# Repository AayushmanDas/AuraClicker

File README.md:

# ⚡ AuraClicker

A compact, battery-powered custom macro-pad and wireless input controller powered by the **ESP32-C3** RISC-V microcontroller. 

Designed natively in **KiCad** with end-to-end Design for Manufacturing (DFM) verification, ready for turnkey fabrication and assembly via JLCPCB SMT services.

---

## 📸 Media & Previews

| 3D PCB Preview | JLCPCB DFM Placement |
| :---: | :---: |
|  |  |

---

## ✨ Key Features

* **MCU Core:** ESP32-C3 RISC-V SoC (2.4 GHz Wi-Fi & Bluetooth 5 LE).
* **Power & Battery Management:**
  * Dedicated **TP4056** Li-Po linear charging IC over USB-C.
  * **AMS1117-3.3** high-current LDO for clean 3.3V power distribution.
  * 2-Pin **Molex PicoBlade (1.25mm)** battery connector. Recommended to be used with 3.7-4.2V 500mAh LiPo battery.
  * Hardware SPDT power slide switch (`SW1`).
* **Inputs & Peripherals:**
  * 4x Low-profile tactile click buttons (`SW2` – `SW5`) arranged for ergonomic thumb/finger reach.
  * Status LEDs for battery activity and low-power telemetry.
* **Programming & Debugging:**
  * Standard 1x6 (2.54mm) FTDI / UART header (`BERG1`) for serial programming and debug monitoring.

---

## 🗂️ Repository Structure

```text
AuraClicker/
├── kicad/                        # Raw KiCad project and PCB design files
│   ├── AuraClicker.kicad_pro
│   ├── AuraClicker.kicad_sch
│   ├── AuraClicker.kicad_pcb
│   ├── fp-lib-table
│   └── Team_Antarez_Logo.kicad_mod
│
├── production/                   # Fabrication-ready packages & CAD files
│   ├── AuraClicker_Fabrication.zip   # Gerber package ready for JLCPCB/PCBWay
│   ├── AuraClicker_BOM.xlsx          # Bill of Materials with LCSC part numbers
│   ├── AuraClicker_Placement.xlsx    # Pick & Place / Centroid coordinate file (.pos)
│   ├── AuraClicker_schem.pdf         # Printable PDF schematic
│   └── AuraClicker_Model.step        # Centered-origin 3D CAD STEP model
│
├── media/                        # Renders, schematics, and DFM validation captures
├── LICENSE
└── README.md
```

---

## 📌 Hardware Pin Mapping

| Peripheral | Reference | Net / Function | Active State |
| :--- | :--- | :--- | :--- |
| **Button 1** | `SW2` | Tactile Input | Active Low (Pull-up) |
| **Button 2** | `SW3` | Tactile Input | Active Low (Pull-up) |
| **Button 3** | `SW4` | Tactile Input | Active Low (Pull-up) |
| **Button 4** | `SW5` | Tactile Input | Active Low (Pull-up) |
| **Activity LED** | `D1` / `ACTIVITY1` | System Telemetry | Active High |
| **Low Batt LED** | `D2` / `LOW_BATT1` | Battery Warning | Active High |
| **Power Switch** | `SW1` | VBAT / VBUS Select | Hardware Cutoff |
| **UART Port** | `BERG1` | TX / RX / GND / 3V3 / DTR / RTS | 3.3V TTL Level |

---

## ⚠️ DFM Review & Assembly Notes (JLCPCB PCBA)

When placing a PCBA order via JLCPCB, verify the following manual adjustments during the **DFM Placement Review** step:

1. **`BERG1` (1x6 2.54mm Pin Header):**
   * *Rotation / Offset:* Rotate 90° and verify the 6 pins align over the through-hole pattern.
   * *Note:* If using **Economic PCBA**, through-hole components are not populated by default. Hand-solder this header manually upon delivery.
2. **`BM1` (USB-C 16-Pin Receptacle):**
   * *Placement:* Shift the component forward/inward along the Y-axis so the SMT signal pins land centered on the pads and the mechanical shield legs seat cleanly in their plated slots.
3. **`JST1` (Molex PicoBlade 1.25mm Header):**
   * *Placement:* Shift the component slightly inward (away from the outer PCB edge) along the Y-axis until the rear signal leads and side mechanical retention tabs center on their respective footprint pads.

---

## 🛠️ Fabrication & Ordering Quickstart

1. **Bare PCB Only:** Upload `production/Gerbers_AuraClicker.zip` to JLCPCB (FR-4, 1.6mm thickness, standard 2-layer).
2. **SMT Assembly:**
   * Enable **SMT Assembly**.
   * Upload `production/BOM_AuraClicker.csv` for the component list.
   * Upload `production/CPL_AuraClicker.csv` for pick-and-place centroid positions.
   * Product Category Recommendation: `Reserch\Education\DIY\Entertainment -> DIY Hobby Circuit Board` (*HS Code: 902300*).

---

## 📜 License & Trademark Notice

* **Hardware & Schematics:** Distributed under the **MIT License**. Feel free to modify, build, and redistribute the board.
* **Branding & Logos:** The **Team Antarez** insignia, logo graphics, and name are proprietary trademarks of Team Antarez. All rights reserved. You are free to manufacture and modify the hardware, but please remove proprietary team insignias from derivative or commercial releases.

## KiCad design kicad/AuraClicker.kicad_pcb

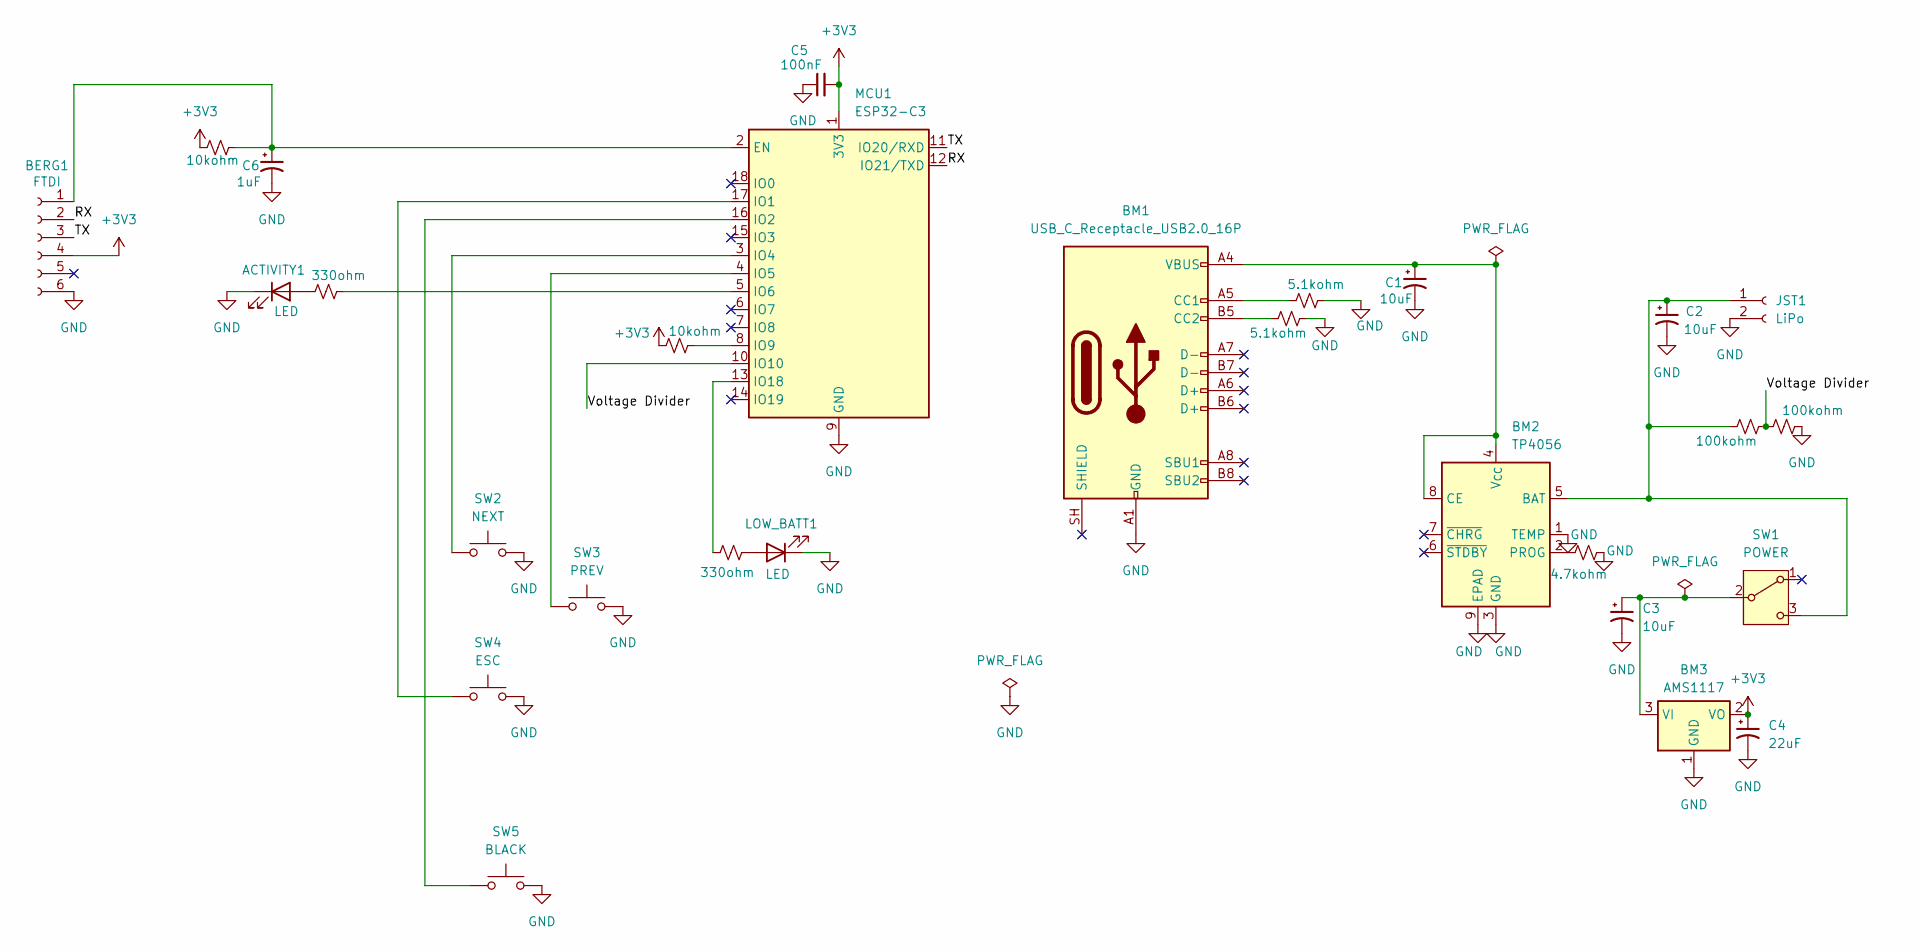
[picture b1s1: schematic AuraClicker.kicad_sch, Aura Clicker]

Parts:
ACTIVITY1: LED; LED_0603_1608Metric; MPN YLED0603G; LCSC Part Number C19273151
BERG1: FTDI; PinHeader_1x06_P2.54mm_Vertical; MPN PH2.54-06PB2G-H25; LCSC Part Number C42431807
BM1: USB_C_Receptacle_USB2.0_16P; USB_C_Receptacle_HRO_TYPE-C-31-M-12; MPN HX USB3.1TYPE-C-16P FS; LCSC Part Number C41427498
BM2: TP4056; SOIC-8-1EP_3.9x4.9mm_P1.27mm_EP2.41x3.3mm_ThermalVias; MPN TP4056; LCSC Part Number C382139
BM3: AMS1117; SOT-223-3_TabPin2; MPN AMS1117-3.3; LCSC Part Number C6186
C1, C2, C3: 10uF; C_0603_1608Metric; MPN TMCJ0J106MTRF; LCSC Part Number C1953982
C4: 22uF; C_1206_3216Metric; MPN TAJA226M016RNJ; LCSC Part Number C6328904
C5: 100nF; C_0603_1608Metric; MPN CC0603KRX7R9BB104; LCSC Part Number C14663
C6: 1uF; C_0603_1608Metric; MPN TACL105K016XTA; LCSC Part Number C1952789
JST1: LiPo; Molex_PicoBlade_53261-0271_1x02-1MP_P1.25mm_Horizontal; MPN S2B-PH-K(LF)(SN); LCSC Part Number C265016
LOW_BATT1: LED; LED_0603_1608Metric; MPN YLED0603G; LCSC Part Number C19273151
MCU1: ESP32-C3; ESP32-C3-WROOM-02; MPN ESP32-C3-WROOM-02-N4; LCSC Part Number C2934560
R1, R2: 5.1kohm; R_0603_1608Metric; MPN FRC0603F5101TS; LCSC Part Number C2907044
R3: 4.7kohm; R_0603_1608Metric; MPN RC0603FR-074K7L; LCSC Part Number C99782
R6, R7: 10kohm; R_0603_1608Metric; MPN RC0603FR-0710KL; LCSC Part Number C98220
R8, R9: 100kohm; R_0603_1608Metric; MPN RC0603FR-07100KL; LCSC Part Number C14675
R10, R12: 330ohm; R_0603_1608Metric; MPN RC0603FR-07330RL; LCSC Part Number C105881
SW1: POWER; SW_SPDT_PCM12; MPN MST-12D18G4 SPDT Slide Switch; LCSC Part Number C49023767
SW2: NEXT; SW_Push_1P1T_NO_E-Switch_TL3301NxxxxxG; MPN SH-6X6X5H-TP; LCSC Part Number C42416254
SW3: PREV; SW_Push_1P1T_NO_E-Switch_TL3301NxxxxxG; MPN SH-6X6X5H-TP; LCSC Part Number C42416254
SW4: ESC; SW_Push_1P1T_NO_E-Switch_TL3301NxxxxxG; MPN SH-6X6X5H-TP; LCSC Part Number C42416254
SW5: BLACK; SW_Push_1P1T_NO_E-Switch_TL3301NxxxxxG; MPN SH-6X6X5H-TP; LCSC Part Number C42416254

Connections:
+3V3: BERG1.4, BM3.2 (VO), C4.1, C5.2, MCU1.1 (3V3), R6.1, R7.1
/RX: BERG1.2, MCU1.12 (IO21/TXD)
/TX: BERG1.3, MCU1.11 (IO20/RXD)
/Voltage Divider: MCU1.10 (IO10), R8.2, R9.1
GND: ACTIVITY1.1 (K), BERG1.6, BM1.A1 (GND), BM1.A12 (GND), BM1.B1 (GND), BM1.B12 (GND), BM2.1 (TEMP), BM2.3 (GND), BM2.9 (EPAD), BM3.1 (GND), C1.2, C2.2, C3.2, C4.2, C5.1, C6.2, JST1.2, LOW_BATT1.1 (K), MCU1.9 (GND), MCU1.19 (GND), R1.2, R2.2, R3.2, R9.2, SW2.2, SW3.2, SW4.2, SW5.2
unnamed: ACTIVITY1.2 (A), R10.1
unnamed: BERG1.1, C6.1, MCU1.2 (EN), R6.2
unnamed: BM1.A5 (CC1), R1.1
unnamed: BM1.B5 (CC2), R2.1
unnamed: BM2.5 (BAT), C2.1, JST1.1, R8.1, SW1.3 (C)
unnamed: BM1.A4 (VBUS), BM1.A9 (VBUS), BM1.B4 (VBUS), BM1.B9 (VBUS), BM2.4 (V_{CC}), BM2.8 (CE), C1.1
unnamed: BM2.2 (PROG), R3.1
unnamed: BM3.3 (VI), C3.1, SW1.2 (B)
unnamed: LOW_BATT1.2 (A), R12.1
unnamed: MCU1.17 (IO1), SW4.1
unnamed: MCU1.16 (IO2), SW5.1
unnamed: MCU1.3 (IO4), SW2.1
unnamed: MCU1.4 (IO5), SW3.1
unnamed: MCU1.5 (IO6), R10.2
unnamed: MCU1.8 (IO9), R7.2
unnamed: MCU1.13 (IO18), R12.2

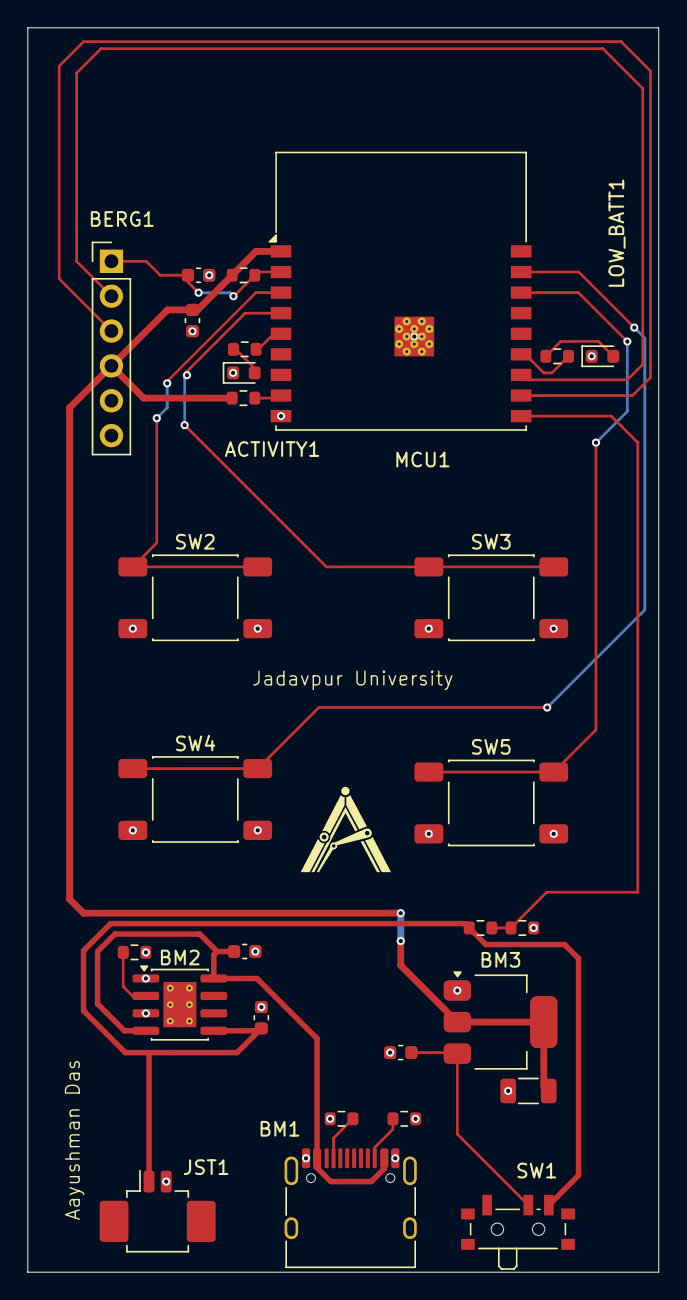
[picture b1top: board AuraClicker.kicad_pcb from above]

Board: 2 copper layers, 46.0 x 90.7 mm, 28 parts (0 on the bottom side), 21 nets.

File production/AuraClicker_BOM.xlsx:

Serial Number | Manufacturing Part Number (MPN) | LCSC Part # | Designator | Quantity | Value | Footprint | Top/Bottom | Points (No. of Pins) | Comments
1 | KT-0603R | C2286 | ACTIVITY1,LOW_BATT1 | 2 | LED | LED_SMD:LED_0603_1608Metric | Top | 2
2 | PH2.54-06PB2G-H25 | C42431807 | BERG1 | 1 | FTDI | Connector_PinHeader_2.54mm:PinHeader_1x06_P2.54mm_Vertical | Top | 6
3 | HX USB3.1TYPE-C-16P FS | C41427498 | BM1 | 1 | USB_C_Receptacle_USB2.0_16P | Connector_USB:USB_C_Receptacle_HRO_TYPE-C-31-M-12 | Top | 16
4 | TP4056-42-ESOP8 | C16581 | BM2 | 1 | TP4056 | Package_SO:SOIC-8-1EP_3.9x4.9mm_P1.27mm_EP2.41x3.3mm_ThermalVias | Top | 9
5 | AMS1117-3.3 | C6186 | BM3 | 1 | AMS1117 | Package_TO_SOT_SMD:SOT-223-3_TabPin2 | Top | 4
6 | CL10A106KP8NNNC | C19702 | C1,C2,C3 | 3 | 10uF | Capacitor_SMD:C_0603_1608Metric | Top | 2
7 | CL31A226KAHNNNE | C12891 | C4 | 1 | 22uF | Capacitor_SMD:C_1206_3216Metric | Top | 2
8 | CC0603KRX7R9BB104 | C14663 | C5 | 1 | 100nF | Capacitor_SMD:C_0603_1608Metric | Top | 2
9 | CL10A105KB8NNNC | C15849 | C6 | 1 | 1uF | Capacitor_SMD:C_0603_1608Metric | Top | 2
10 | 1.25T-2PSurface Mount, Right Angle | C22074 | JST1 | 1 | LiPo | Connector_JST:JST_PH_B2B-PH-K_1x02_P2.00mm_Vertical | Top | 2
11 | ESP32-C3-WROOM-02-N4 | C2934560 | MCU1 | 1 | ESP32-C3 | RF_Module:ESP32-C3-WROOM-02 | Top | 19
12 | 0603WAF5101T5E | C23186 | R1,R2 | 2 | 5.1kohm | Resistor_SMD:R_0603_1608Metric | Top | 2
13 | 0603WAF4701T5E | C23162 | R3 | 1 | 4.7kohm | Resistor_SMD:R_0603_1608Metric | Top | 2
14 | 0603WAF1002T5E | C25804 | R6,R7 | 2 | 10kohm | Resistor_SMD:R_0603_1608Metric | Top | 2
15 | 0603WAF1003T5E | C25803 | R8,R9 | 2 | 100kohm | Resistor_SMD:R_0603_1608Metric | Top | 2
16 | 0603WAF3300T5E | C23138 | R10,R12 | 2 | 330ohm | Resistor_SMD:R_0603_1608Metric | Top | 2
17 | PCM12SMTR | C221841 | SW1 | 1 | POWER | Button_Switch_SMD:SW_SPDT_PCM12 | Top | 3
18 | SH-6X6X5H-TP | C42416254 | SW2 | 1 | NEXT | Button_Switch_SMD:SW_Push_1P1T_NO_E-Switch_TL3301NxxxxxG | Top | 4
19 | SH-6X6X5H-TP | C42416254 | SW3 | 1 | PREV | Button_Switch_SMD:SW_Push_1P1T_NO_E-Switch_TL3301NxxxxxG | Top | 4
20 | SH-6X6X5H-TP | C42416254 | SW4 | 1 | ESC | Button_Switch_SMD:SW_Push_1P1T_NO_E-Switch_TL3301NxxxxxG | Top | 4
21 | SH-6X6X5H-TP | C42416254 | SW5 | 1 | BLACK | Button_Switch_SMD:SW_Push_1P1T_NO_E-Switch_TL3301NxxxxxG | Top | 4
